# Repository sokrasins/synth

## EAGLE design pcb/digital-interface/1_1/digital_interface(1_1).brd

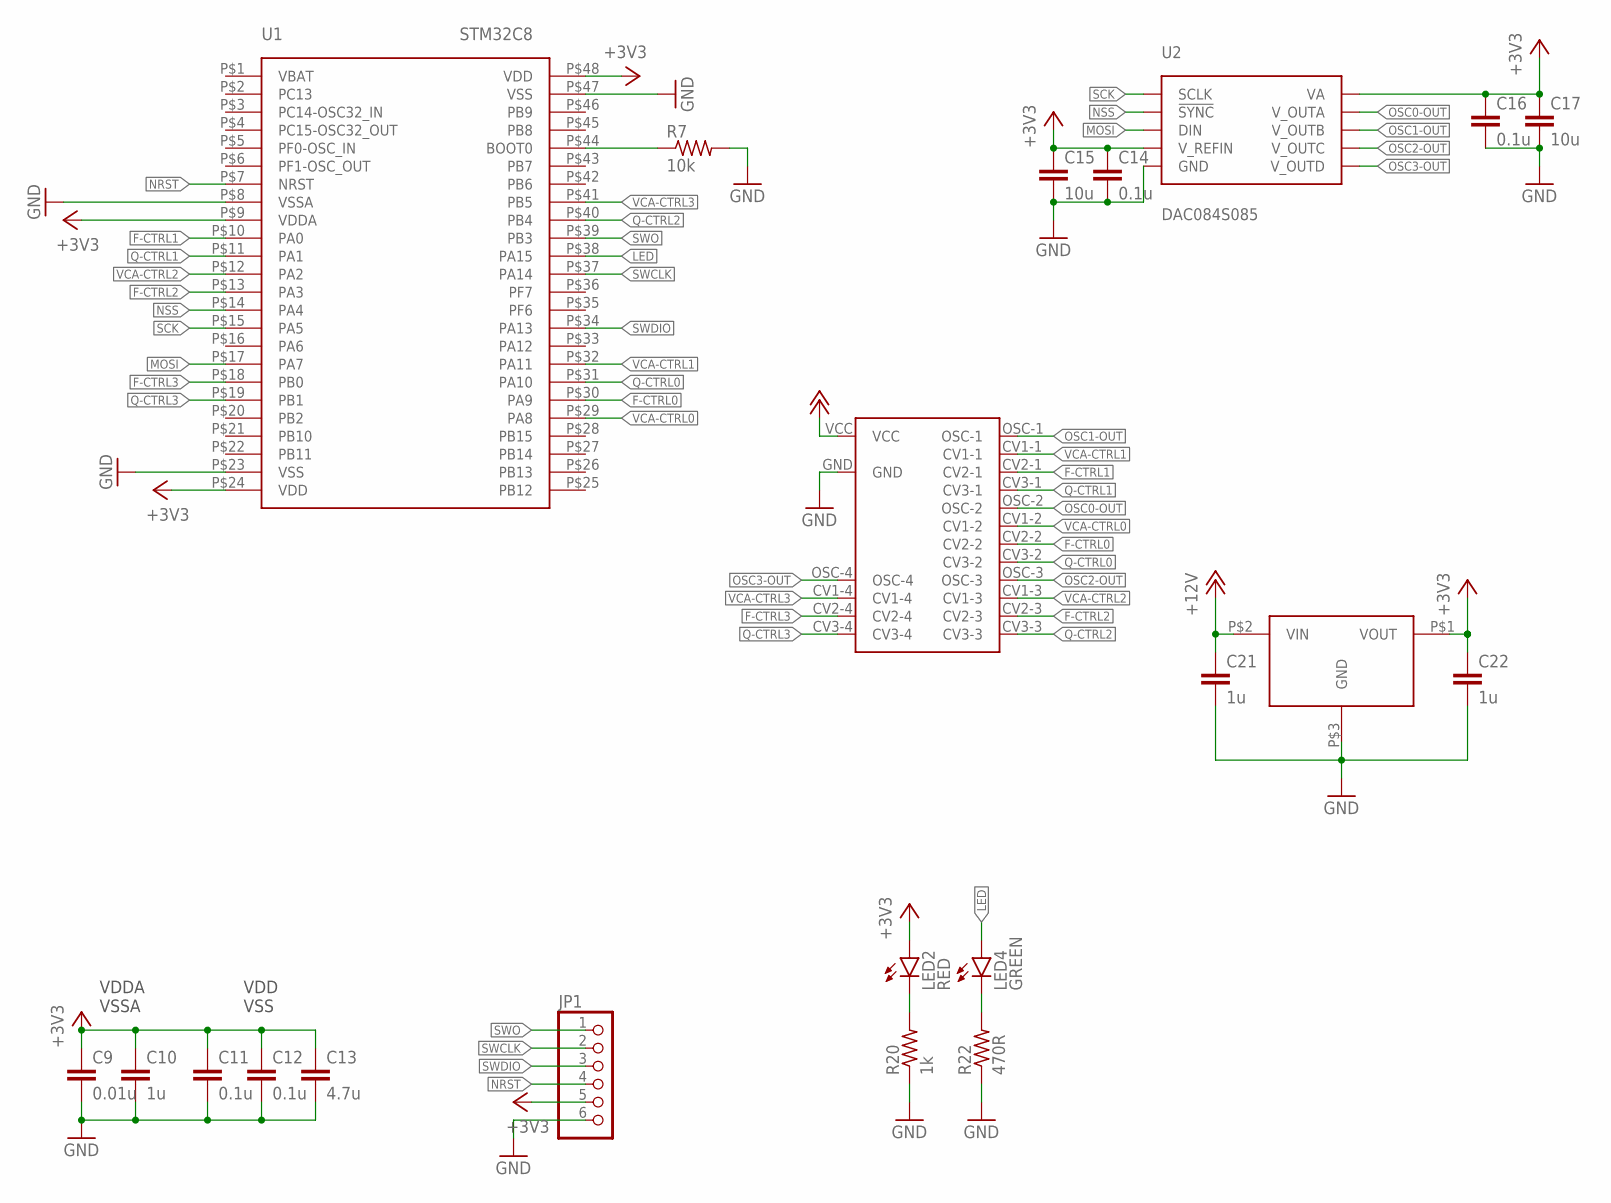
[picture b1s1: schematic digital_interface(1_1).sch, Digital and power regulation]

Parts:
C9: 0.01u; C0603
C10, C21, C22: 1u; C0603
C11, C12, C14, C16: 0.1u; C0603
C13: 4.7u; C0603
C15, C17: 10u; C0603
JP1: PINHD-1X6; 1X06
LED2: RED; 1206
LED4: GREEN; 1206
R7: 10k; R0603
R20: 1k; R0603
R22: 470R; R0603
U1: STM32C8; LQFP48
U2: DAC084S085; VSSOP10
U3: TLV760; SOT23-3
U$1: CV_MODULE

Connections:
+3V3: C9.1, C10.1, C11.1, C12.1, C13.1, C14.1, C15.1, C16.1, C17.1, C22.1, JP1.5, LED2.A, U1.P$9 (VDDA), U1.P$24 (VDD), U1.P$48 (VDD), U2.P$1 (VA), U2.P$7 (V_REFIN), U3.P$1 (VOUT)
+12V: C21.1, U3.P$2 (VIN), U$1.VCC
F-CTRL0: U1.P$30 (PA9), U$1.CV2-2
F-CTRL1: U1.P$10 (PA0), U$1.CV2-1
F-CTRL2: U1.P$13 (PA3), U$1.CV2-3
F-CTRL3: U1.P$18 (PB0), U$1.CV2-4
GND: C9.2, C10.2, C11.2, C12.2, C13.2, C14.2, C15.2, C16.2, C17.2, C21.2, C22.2, JP1.6, R7.2, R20.1, R22.1, U1.P$8 (VSSA), U1.P$23 (VSS), U1.P$47 (VSS), U2.P$6 (GND), U3.P$3 (GND), U$1.GND
LED: LED4.A, U1.P$38 (PA15)
MOSI: U1.P$17 (PA7), U2.P$8 (DIN)
unnamed: R7.1, U1.P$44 (BOOT0)
unnamed: LED2.C, R20.2
unnamed: LED4.C, R22.2
NRST: JP1.4, U1.P$7 (NRST)
NSS: U1.P$14 (PA4), U2.P$9 (!SYNC)
OSC0-OUT: U2.P$2 (V_OUTA), U$1.OSC-2
OSC1-OUT: U2.P$3 (V_OUTB), U$1.OSC-1
OSC2-OUT: U2.P$4 (V_OUTC), U$1.OSC-3
OSC3-OUT: U2.P$5 (V_OUTD), U$1.OSC-4
Q-CTRL0: U1.P$31 (PA10), U$1.CV3-2
Q-CTRL1: U1.P$11 (PA1), U$1.CV3-1
Q-CTRL2: U1.P$40 (PB4), U$1.CV3-3
Q-CTRL3: U1.P$19 (PB1), U$1.CV3-4
SCK: U1.P$15 (PA5), U2.P$10 (SCLK)
SWCLK: JP1.2, U1.P$37 (PA14)
SWDIO: JP1.3, U1.P$34 (PA13)
SWO: JP1.1, U1.P$39 (PB3)
VCA-CTRL0: U1.P$29 (PA8), U$1.CV1-2
VCA-CTRL1: U1.P$32 (PA11), U$1.CV1-1
VCA-CTRL2: U1.P$12 (PA2), U$1.CV1-3
VCA-CTRL3: U1.P$41 (PB5), U$1.CV1-4

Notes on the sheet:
VDDA VSSA
VDD VSS

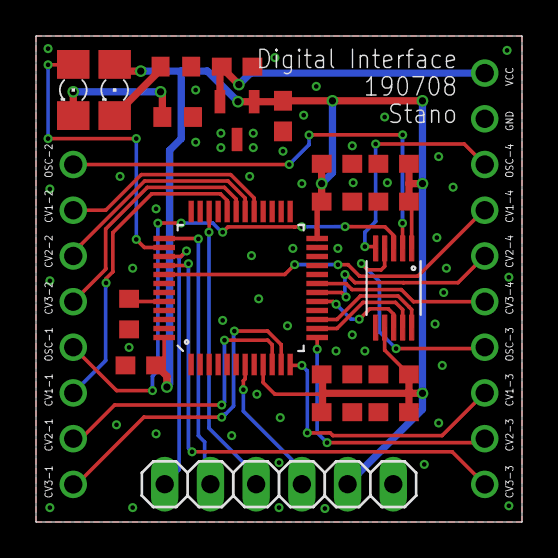
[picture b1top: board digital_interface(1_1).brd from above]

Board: 2 copper layers, 27.0 x 27.0 mm, 21 parts (0 on the bottom side), 30 nets.

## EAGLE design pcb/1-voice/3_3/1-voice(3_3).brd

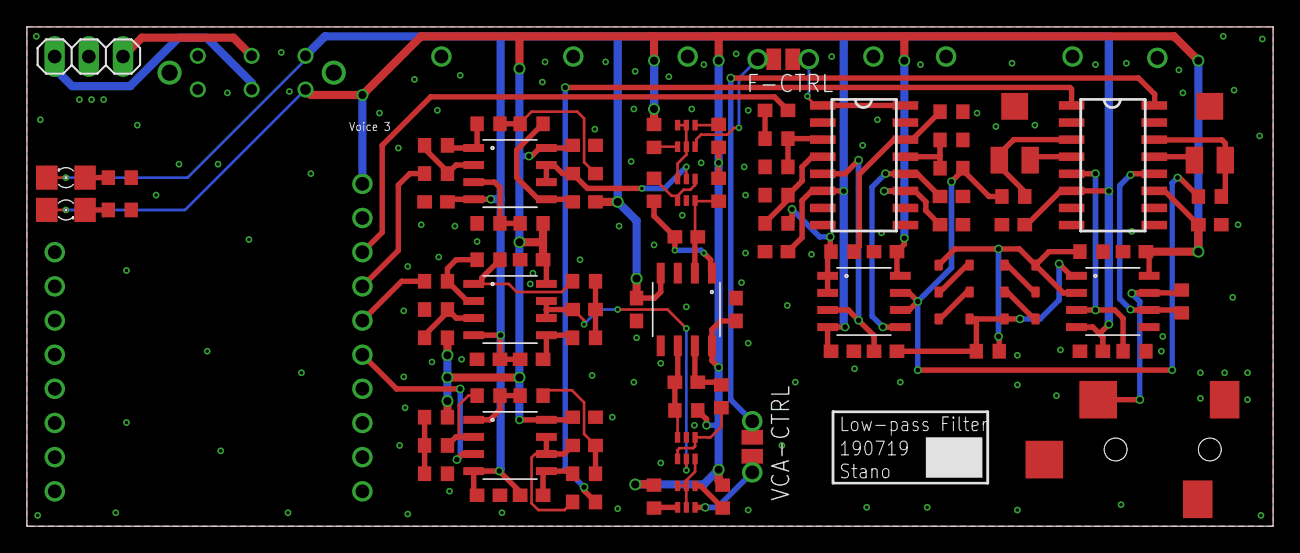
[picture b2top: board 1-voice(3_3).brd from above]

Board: 2 copper layers, 92.6 x 37.1 mm, 98 parts (0 on the bottom side), 68 nets.

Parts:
C1, C20: 10p; C0603
C2: 10u; C0603
C3, C23, C28: 1000p; C0603
C4, C24, C27, C35, C36: 2000p; C0603
C5, C6, C7, C8, C18, C19, C25, C26, C29, C30, C31, C32, C33, C34, C37, C38: 0.1u; C0603
D1, D2, D3, D4, D5, D6: 1N4148; SOD-323
JP2: 1X03
JP7: TRS
LED1: BLUE; 1206
LED3: YELLOW; 1206
Q1, Q3: BC847BS; SOT-363-JBLMASK
Q2, Q4: BC857BS; SOT-363-JBLMASK
R1, R36, R38: 3.3k; R0603
R2, R25, R45: 30k; R0603
R3, R4, R5, R10, R11, R12, R21, R26, R29, R33, R35, R37, R43, R44: 10k; R0603
R6, R13: 165k; R0603
R8, R14: 1k; R0603
R9: 280k; R0603
R15, R17: 562; R0603
R16, R18: 72k; R0603
R19, R39: 100k; R0603
R23, R24, R31, R46: 10; R0603
R27, R30, R32, R34: 220; R0603
R28: 562k; R0603
R40: 14.7k; R0603
R41: 1.62k; R0603
R42: 8.45k; R0603
SW1: SWITCH-DPDT; DPDT
U4, U5, U7, U9, U10, U11: TL072; SOIC8
U6, U8: LM13700; DMP16
U$1: CV_MODULE
U$2, U$3: CURRENT_TESTPOINT
VR1, VR2: 1k; POT-TRIM-SMD-BOURNS-3314

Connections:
12V-IN: JP2.3, SW1.P$5
+12V: C5.2, C8.2, C18.2, C25.2, C29.1, C31.2, C33.1, C37.1, LED1.A, R9.2, R16.1, R18.1, R23.2, R24.2, R28.2, R31.2, R42.2, R46.2, SW1.P$4, U4.P$8, U5.P$8, U6.11, U7.P$8, U8.11, U9.P$8, U10.P$8, U11.P$8, U$1.VCC
-12V: C3.2, C6.1, C7.1, C19.1, C23.2, C26.1, C28.2, C30.2, C32.1, C34.2, C38.2, LED3.C, SW1.P$1, U4.P$4, U5.P$4, U6.6, U7.P$4, U8.6, U9.P$4, U10.P$4, U11.P$4
-12V-IN: JP2.1, SW1.P$2
F0-OUT: R2.1, R25.2, R35.2, U7.P$6, U7.P$7
F-CTRL0: R13.2, U$1.CV1-4
F-CTRL0-EXP: U6.1, U6.16, U$2.P1, U$2.P1.1
F-CTRL0-LIN: C24.2, Q1.2, U4.P$6, U4.P$7
FILT_IN: C2.2, R26.1
GND: C5.1, C6.2, C7.2, C8.1, C18.1, C19.2, C25.1, C26.2, C29.2, C30.1, C31.1, C32.2, C33.2, C34.1, C36.2, C37.2, C38.1, JP2.2, JP7.P$1, Q1.5, Q3.2, R15.2, R17.2, R19.1, R21.1, R27.1, R30.2, R32.2, R34.2, R36.1, R38.1, R41.1, U9.P$3, U9.P$5, U11.P$5, U$1.GND, VR1.2, VR2.2
unnamed: R10.2, R13.1, U4.P$2
unnamed: R1.2, U8.12, U11.P$6
unnamed: R2.2, U8.14, VR2.1
unnamed: C3.1, R3.2, U10.P$5
unnamed: C4.1, R3.1, R4.2
unnamed: R4.1, R5.1, U10.P$1
unnamed: Q2.6, U$2.P2, U$2.P2.1
unnamed: Q4.6, U$3.P2, U$3.P2.1
unnamed: Q1.1, Q1.4, R8.2
unnamed: C20.2, R8.1, U9.P$1
unnamed: C20.1, Q1.6, R9.1, U9.P$2
unnamed: C23.1, R11.2, U4.P$5
unnamed: Q1.3, Q2.2, Q2.3, Q2.5
unnamed: C24.1, R11.1, R12.2
unnamed: R10.1, R12.1, U4.P$1
unnamed: Q3.1, Q3.4, R14.2
unnamed: LED1.C, R19.2
unnamed: R5.2, R6.1, U10.P$2
unnamed: R15.1, R16.2, U4.P$3
unnamed: LED3.A, R21.2
unnamed: Q2.4, R23.1
unnamed: Q2.1, R24.1
unnamed: C36.1, U6.12, U7.P$5
unnamed: R26.2, R27.2, U6.3
unnamed: C35.1, U6.5, U7.P$3
unnamed: R36.2, U8.5, U11.P$3
unnamed: U8.4, VR1.1
unnamed: R29.1, R30.1, U6.4
unnamed: D1.2, D6.1, R37.1, R38.2, U11.P$2
unnamed: C1.2, R14.1, U9.P$7
unnamed: C35.2, D3.1, D4.2, R37.2, U11.P$1
unnamed: R32.1, R33.2, U6.14
unnamed: R34.1, R35.1, U6.13
unnamed: D2.1, D3.2
unnamed: D1.1, D2.2
unnamed: D4.1, D5.2
unnamed: D5.1, D6.2
unnamed: R40.1, R41.2, R42.1
unnamed: R39.1, R40.2, U5.P$2
unnamed: R39.2, R43.1, U5.P$1
unnamed: C27.1, R43.2, R44.1
unnamed: C28.1, R44.2, U5.P$5
unnamed: R45.1, U8.1
unnamed: U8.13, VR2.3
unnamed: C1.1, Q3.3, R28.1, U9.P$6
unnamed: R29.2, R33.1, U7.P$1, U7.P$2
unnamed: R17.1, R18.2, U10.P$3
unnamed: Q3.6, Q4.2, Q4.3, Q4.5
unnamed: Q4.4, R31.1
unnamed: Q4.1, R46.1
unnamed: R25.1, U8.3, VR1.3
OSC0-OUT: C2.1, U$1.OSC-4
Q-CTRL0: U5.P$3, U$1.CV3-4
Q-CTRL0-I: C27.2, R45.2, U5.P$6, U5.P$7
VCA0-EXP: U8.16, U$3.P1, U$3.P1.1
VCA0-LP: C4.2, Q3.5, U10.P$6, U10.P$7
VCA-CTRL0: R6.2, U$1.CV2-4
VCA-OUT0: JP7.P$2, R1.1, U11.P$7

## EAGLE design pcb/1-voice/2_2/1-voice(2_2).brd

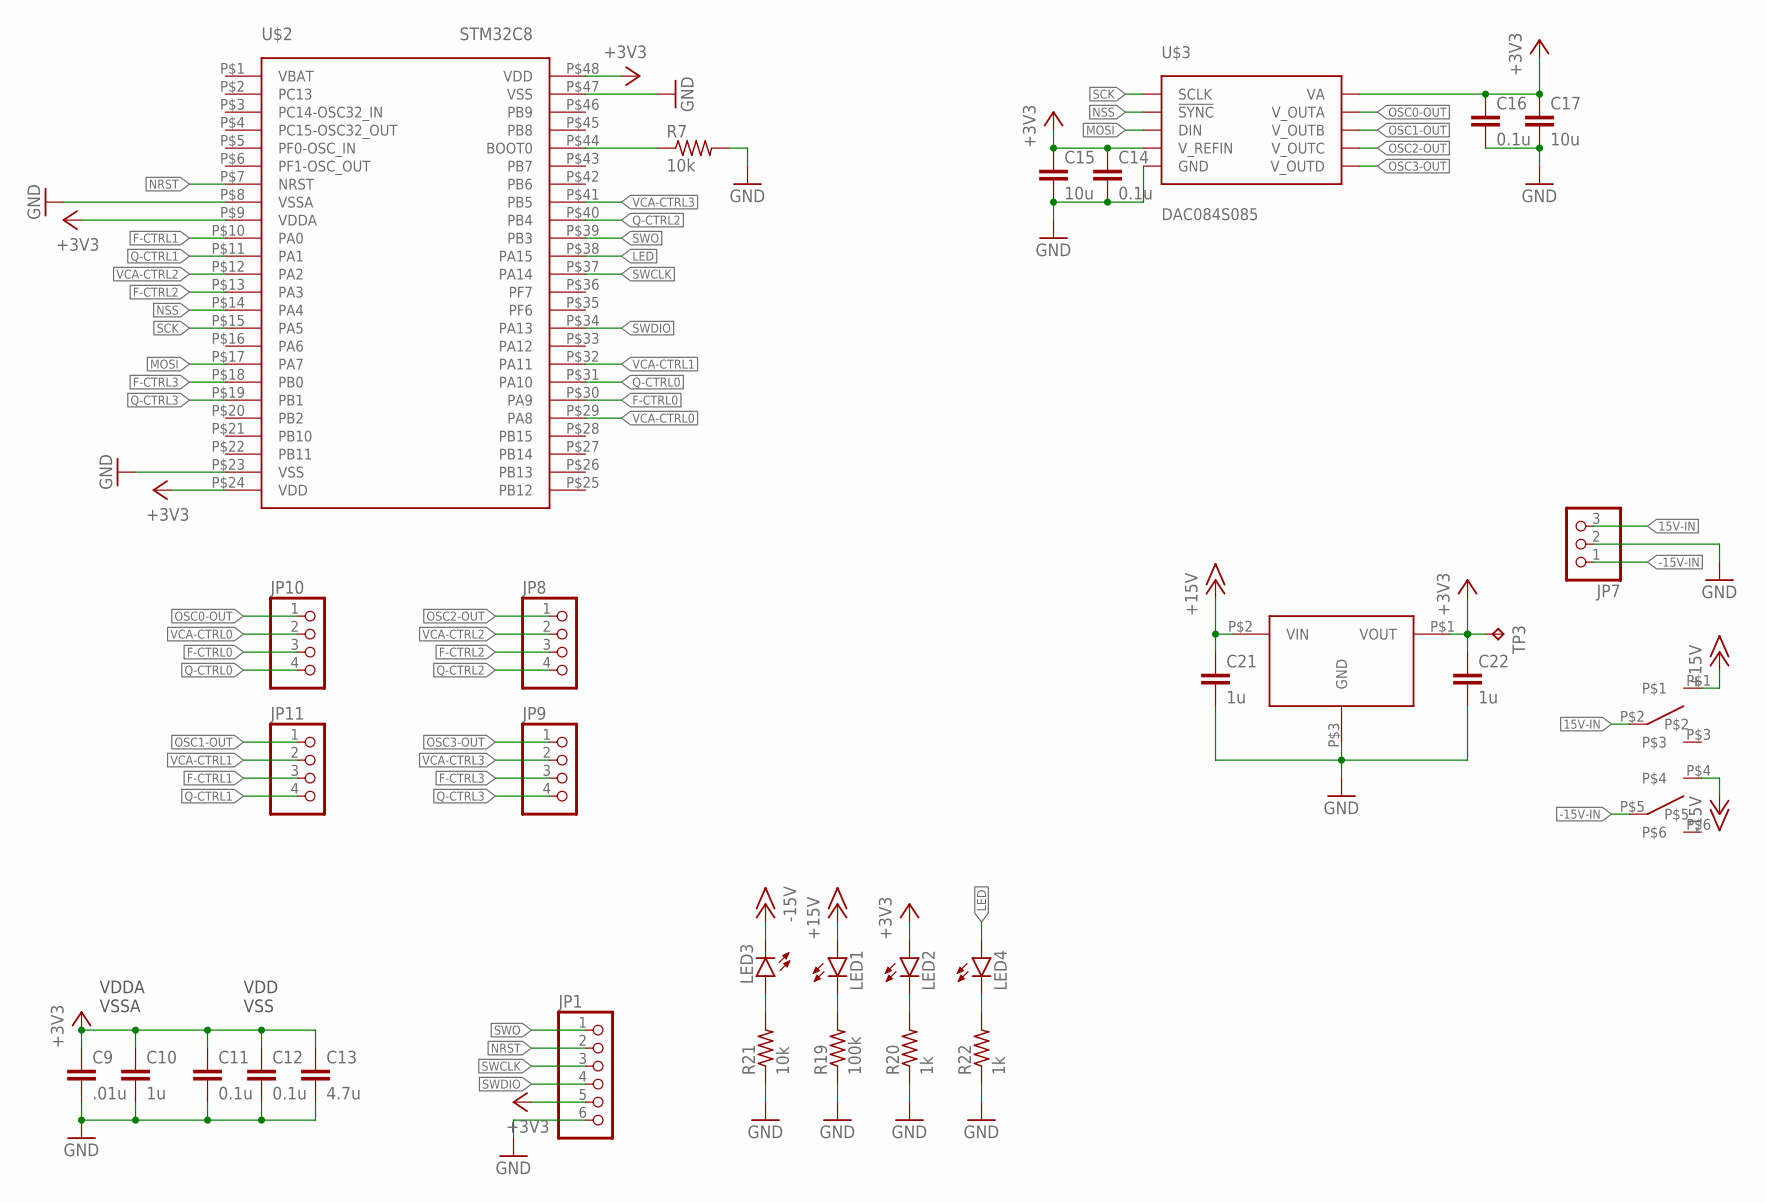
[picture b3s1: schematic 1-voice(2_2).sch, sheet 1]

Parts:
C9: .01u; C0603
C10, C21, C22: 1u; C0603
C11, C12, C14, C16: 0.1u; C0603
C13: 4.7u; C0603
C15, C17: 10u; C0603
JP1: PINHD-1X6; 1X06
JP7: PINHD-1X3; 1X03
JP8, JP9, JP10, JP11: PINHD-1X4; 1X04
LED1, LED2, LED3, LED4: LEDSMT1206; 1206
R7, R21: 10k; R0603
R19: 100k; R0603
R20, R22: 1k; R0603
TP3: TPPAD1-13; P1-13
U$2: STM32C8; LQFP48
U$3: DAC084S085; VSSOP10
U$4: TLV760; SOT23-3
U$6: SWITCH-DPDT; DPDT

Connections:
15V-IN: JP7.3, U$6.P$2
+3V3: C9.1, C10.1, C11.1, C12.1, C13.1, C14.1, C15.1, C16.1, C17.1, C22.1, JP1.5, LED2.A, TP3.TP, U$2.P$9 (VDDA), U$2.P$24 (VDD), U$2.P$48 (VDD), U$3.P$1 (VA), U$3.P$7 (V_REFIN), U$4.P$1 (VOUT); also elsewhere on the board
+15V: C21.1, LED1.A, U$4.P$2 (VIN), U$6.P$1; also elsewhere on the board
-15V: LED3.C, U$6.P$4; also elsewhere on the board
-15V-IN: JP7.1, U$6.P$5
F-CTRL0: JP10.3, U$2.P$30 (PA9); also elsewhere on the board
F-CTRL1: JP11.3, U$2.P$10 (PA0)
F-CTRL2: JP8.3, U$2.P$13 (PA3)
F-CTRL3: JP9.3, U$2.P$18 (PB0)
GND: C9.2, C10.2, C11.2, C12.2, C13.2, C14.2, C15.2, C16.2, C17.2, C21.2, C22.2, JP1.6, JP7.2, R7.2, R19.1, R20.1, R21.1, R22.1, U$2.P$8 (VSSA), U$2.P$23 (VSS), U$2.P$47 (VSS), U$3.P$6 (GND), U$4.P$3 (GND); also elsewhere on the board
LED: LED4.A, U$2.P$38 (PA15)
MOSI: U$2.P$17 (PA7), U$3.P$8 (DIN)
unnamed: R7.1, U$2.P$44 (BOOT0)
unnamed: LED1.C, R19.2
unnamed: LED2.C, R20.2
unnamed: LED3.A, R21.2
unnamed: LED4.C, R22.2
NRST: JP1.2, U$2.P$7 (NRST)
NSS: U$2.P$14 (PA4), U$3.P$9 (!SYNC)
OSC0-OUT: JP10.1, U$3.P$2 (V_OUTA); also elsewhere on the board
OSC1-OUT: JP11.1, U$3.P$3 (V_OUTB)
OSC2-OUT: JP8.1, U$3.P$4 (V_OUTC)
OSC3-OUT: JP9.1, U$3.P$5 (V_OUTD)
Q-CTRL0: JP10.4, U$2.P$31 (PA10)
Q-CTRL1: JP11.4, U$2.P$11 (PA1)
Q-CTRL2: JP8.4, U$2.P$40 (PB4)
Q-CTRL3: JP9.4, U$2.P$19 (PB1)
SCK: U$2.P$15 (PA5), U$3.P$10 (SCLK)
SWCLK: JP1.3, U$2.P$37 (PA14)
SWDIO: JP1.4, U$2.P$34 (PA13)
SWO: JP1.1, U$2.P$39 (PB3)
VCA-CTRL0: JP10.2, U$2.P$29 (PA8); also elsewhere on the board
VCA-CTRL1: JP11.2, U$2.P$32 (PA11)
VCA-CTRL2: JP8.2, U$2.P$12 (PA2)
VCA-CTRL3: JP9.2, U$2.P$41 (PB5)

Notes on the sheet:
VDDA VSSA
VDD VSS

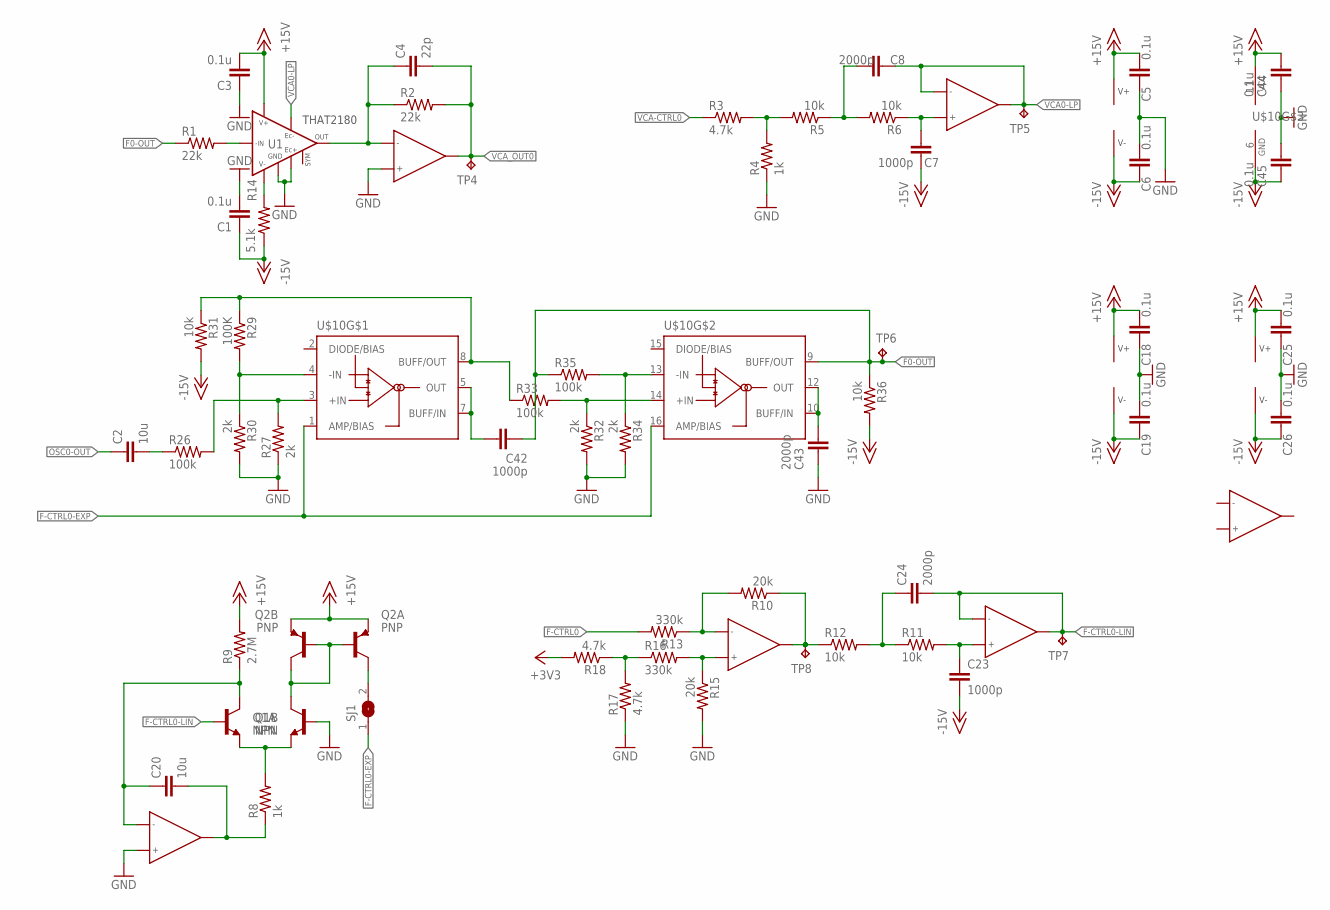
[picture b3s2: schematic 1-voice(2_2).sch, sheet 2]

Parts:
C1, C3, C5, C6, C18, C19, C25, C26, C44, C45: 0.1u; C0603
C2, C20: 10u; C0603
C4: 22p; C0603
C7, C23, C42: 1000p; C0603
C8, C24, C43: 2000p; C0603
Q1: NPN; SOT-363-JBLMASK
Q2: PNP; SOT-363-JBLMASK
R1, R2: 22k; R0603
R3, R17, R18: 4.7k; R0603
R4, R8: 1k; R0603
R5, R6, R11, R12, R31, R36: 10k; R0603
R9: 2.7M; R0603
R10, R15: 20k; R0603
R13, R16: 330k; R0603
R14: 5.1k; R0603
R26, R33, R35: 100k; R0603
R27, R30, R32, R34: 2k; R0603
R29: 100K; R0603
SJ1: SJ
TP4, TP5, TP6, TP7, TP8: TPPAD1-13; P1-13
U1: THAT2180; SIP8
U$1, U$5, U$11: TL072; SOIC8
U$10: XX-13700DMP16; DMP16

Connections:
+3V3: R18.2; also elsewhere on the board
+15V: C3.2, C5.2, C18.2, C25.2, C44.1, Q2.1 (E), Q2.4 (E), R9.2, U1.$P7 (V+), U$1.P$8 (V+), U$5.P$8 (V+), U$10.11 (VCC), U$11.P$8 (V+); also elsewhere on the board
-15V: C1.1, C6.1, C7.1, C19.1, C23.2, C26.1, C45.2, R14.1, R31.2, R36.2, U$1.P$4 (V-), U$5.P$4 (V-), U$10.6 (GND), U$11.P$4 (V-); also elsewhere on the board
F0-OUT: C42.2, R1.1, R35.1, R36.1, TP6.TP, U$10.9 (BUFF/OUT)
F-CTRL0: R13.2; also elsewhere on the board
F-CTRL0-EXP: SJ1.1, U$10.1 (AMP/BIAS), U$10.16 (AMP/BIAS)
F-CTRL0-LIN: C24.2, Q1.2 (B), TP7.TP, U$11.P$6 (IN-), U$11.P$7 (OUT)
FILT_IN: C2.2, R26.1
GND: C1.2, C3.1, C5.1, C6.2, C18.1, C19.2, C25.1, C26.2, C43.2, C44.2, C45.1, Q1.5 (B), R4.1, R15.2, R17.1, R27.1, R30.2, R32.2, R34.2, U1.$P2 (EC+), U1.$P6 (GND), U$1.P$3 (IN+), U$11.P$3 (IN+); also elsewhere on the board
unnamed: R10.2, R13.1, U$5.P$6 (IN-)
unnamed: R1.2, U1.$P1 (-IN)
unnamed: C4.1, R2.1, U1.$P8 (OUT), U$1.P$2 (IN-)
unnamed: R3.2, R4.2, R5.2
unnamed: C8.2, R5.1, R6.2
unnamed: C7.2, R6.1, U$1.P$5 (IN+)
unnamed: Q2.6 (C), SJ1.2
unnamed: Q1.1 (E), Q1.4 (E), R8.2
unnamed: C20.2, R8.1, U$11.P$1 (OUT)
unnamed: C20.1, Q1.6 (C), R9.1, U$11.P$2 (IN-)
unnamed: C23.1, R11.2, U$11.P$5 (IN+)
unnamed: Q1.3 (C), Q2.2 (B), Q2.3 (C), Q2.5 (B)
unnamed: C24.1, R11.1, R12.2
unnamed: R10.1, R12.1, TP8.TP, U$5.P$7 (OUT)
unnamed: R14.2, U1.$P5 (V-)
unnamed: R16.1, R17.2, R18.1
unnamed: R15.1, R16.2, U$5.P$5 (IN+)
unnamed: R26.2, R27.2, U$10.3 (+IN)
unnamed: R29.2, R30.1, U$10.4 (-IN)
unnamed: C42.1, U$10.5 (OUT), U$10.7 (BUFF/IN)
unnamed: R29.1, R31.1, R33.1, U$10.8 (BUFF/OUT)
unnamed: C43.1, U$10.10 (BUFF/IN), U$10.12 (OUT)
unnamed: R32.1, R33.2, U$10.14 (+IN)
unnamed: R34.1, R35.2, U$10.13 (-IN)
OSC0-OUT: C2.1; also elsewhere on the board
VCA0-LP: C8.1, TP5.TP, U1.$P3 (EC-), U$1.P$6 (IN-), U$1.P$7 (OUT)
VCA-CTRL0: R3.1; also elsewhere on the board
VCA_OUT0: C4.2, R2.2, TP4.TP, U$1.P$1 (OUT)

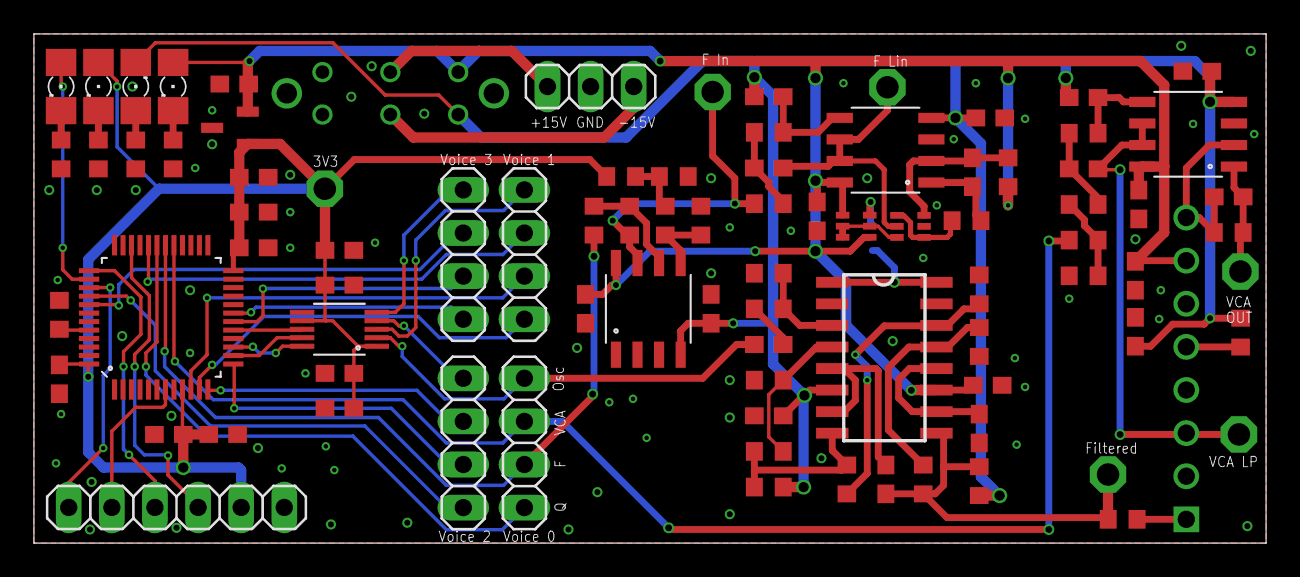
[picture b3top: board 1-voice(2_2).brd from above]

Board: 2 copper layers, 72.6 x 30.0 mm, 90 parts (1 on the bottom side), 65 nets.

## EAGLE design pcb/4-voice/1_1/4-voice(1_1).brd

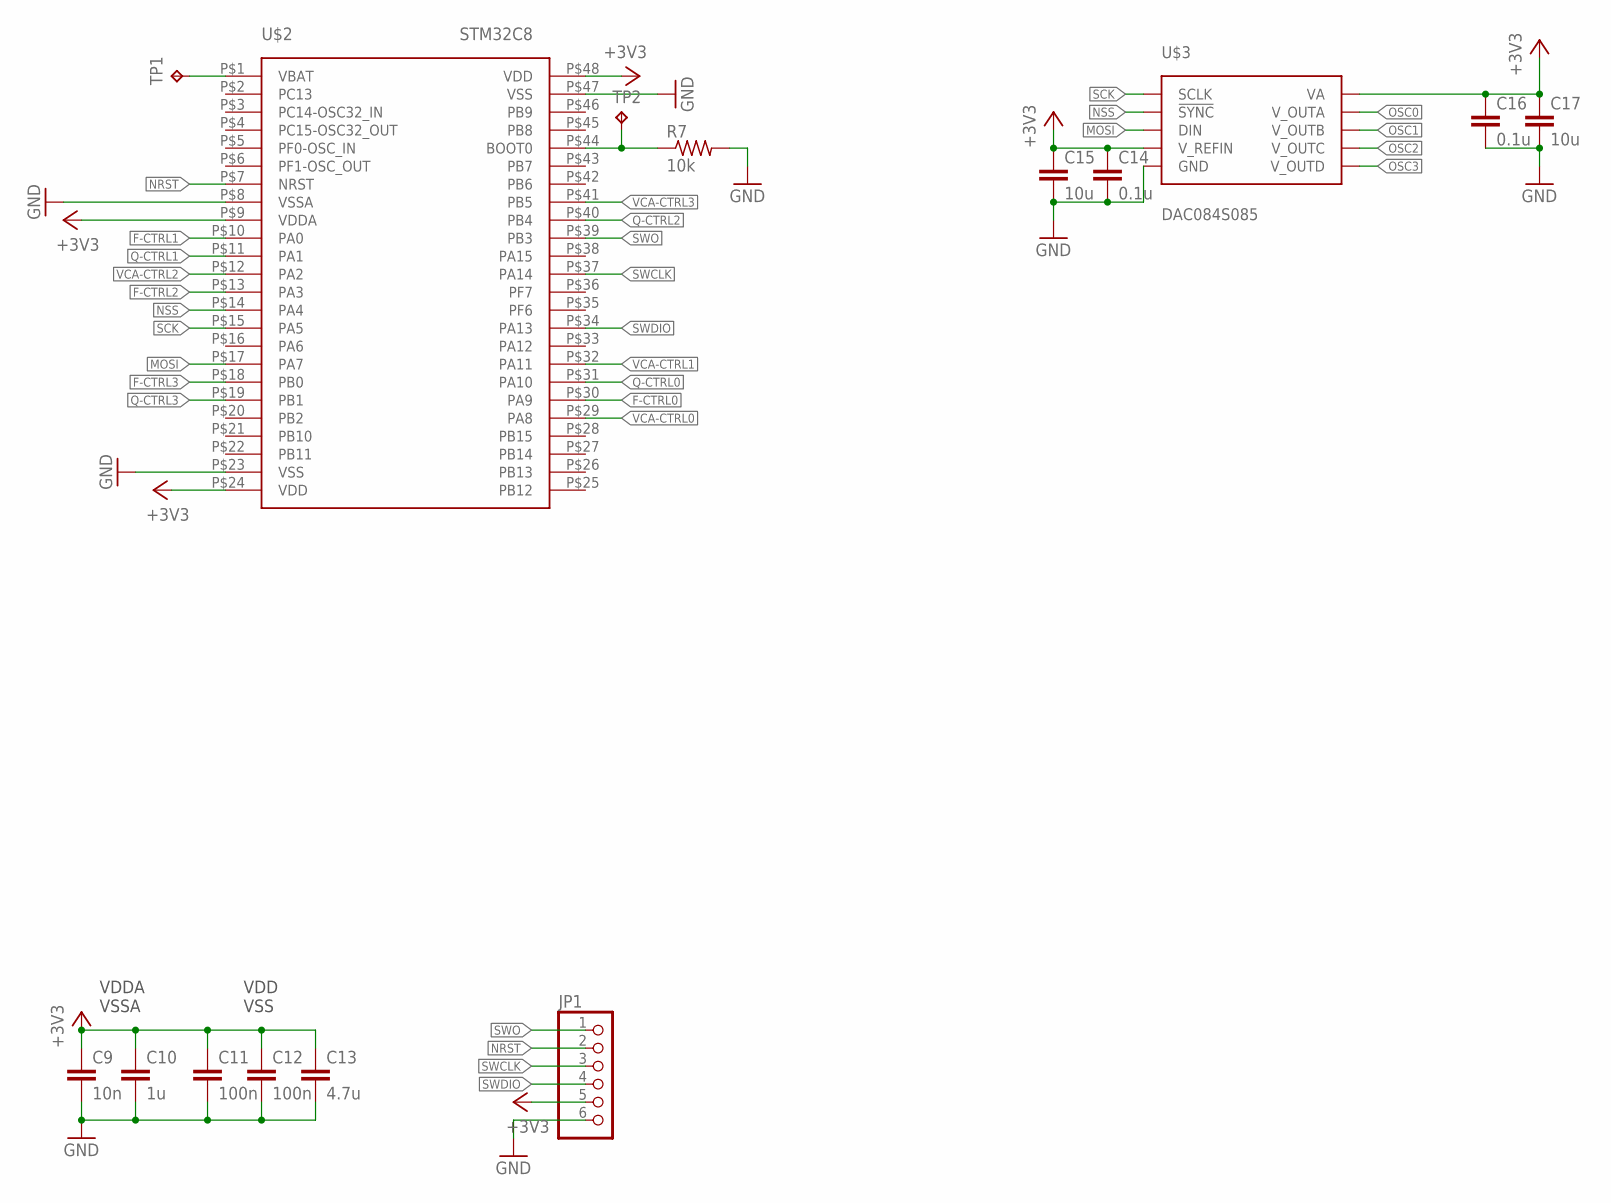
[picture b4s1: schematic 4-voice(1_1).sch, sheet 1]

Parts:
C9: 10n; C1206
C10: 1u; C1206
C11, C12: 100n; C1206
C13: 4.7u; C1206
C14, C16: 0.1u; C1206
C15, C17: 10u; C1206
JP1: PINHD-1X6; 1X06
R7: 10k; R1206
TP1, TP2: TPPAD1-13; P1-13
U$2: STM32C8; LQFP48
U$3: DAC084S085; VSSOP10

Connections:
+3V3: C9.1, C10.1, C11.1, C12.1, C13.1, C14.1, C15.1, C16.1, C17.1, JP1.5, U$2.P$9 (VDDA), U$2.P$24 (VDD), U$2.P$48 (VDD), U$3.P$1 (VA), U$3.P$7 (V_REFIN)
F-CTRL0: U$2.P$30 (PA9)
F-CTRL1: U$2.P$10 (PA0)
F-CTRL2: U$2.P$13 (PA3)
F-CTRL3: U$2.P$18 (PB0)
GND: C9.2, C10.2, C11.2, C12.2, C13.2, C14.2, C15.2, C16.2, C17.2, JP1.6, R7.2, U$2.P$8 (VSSA), U$2.P$23 (VSS), U$2.P$47 (VSS), U$3.P$6 (GND); also elsewhere on the board
MOSI: U$2.P$17 (PA7), U$3.P$8 (DIN)
unnamed: TP1.TP, U$2.P$1 (VBAT)
unnamed: R7.1, TP2.TP, U$2.P$44 (BOOT0)
NRST: JP1.2, U$2.P$7 (NRST)
NSS: U$2.P$14 (PA4), U$3.P$9 (!SYNC)
OSC0: U$3.P$2 (V_OUTA); also elsewhere on the board
OSC1: U$3.P$3 (V_OUTB); also elsewhere on the board
OSC2: U$3.P$4 (V_OUTC); also elsewhere on the board
OSC3: U$3.P$5 (V_OUTD); also elsewhere on the board
Q-CTRL0: U$2.P$31 (PA10)
Q-CTRL1: U$2.P$11 (PA1)
Q-CTRL2: U$2.P$40 (PB4)
Q-CTRL3: U$2.P$19 (PB1)
SCK: U$2.P$15 (PA5), U$3.P$10 (SCLK)
SWCLK: JP1.3, U$2.P$37 (PA14)
SWDIO: JP1.4, U$2.P$34 (PA13)
SWO: JP1.1, U$2.P$39 (PB3)
VCA-CTRL0: U$2.P$29 (PA8); also elsewhere on the board
VCA-CTRL1: U$2.P$32 (PA11); also elsewhere on the board
VCA-CTRL2: U$2.P$12 (PA2); also elsewhere on the board
VCA-CTRL3: U$2.P$41 (PB5); also elsewhere on the board

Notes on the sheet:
VDDA VSSA
VDD VSS

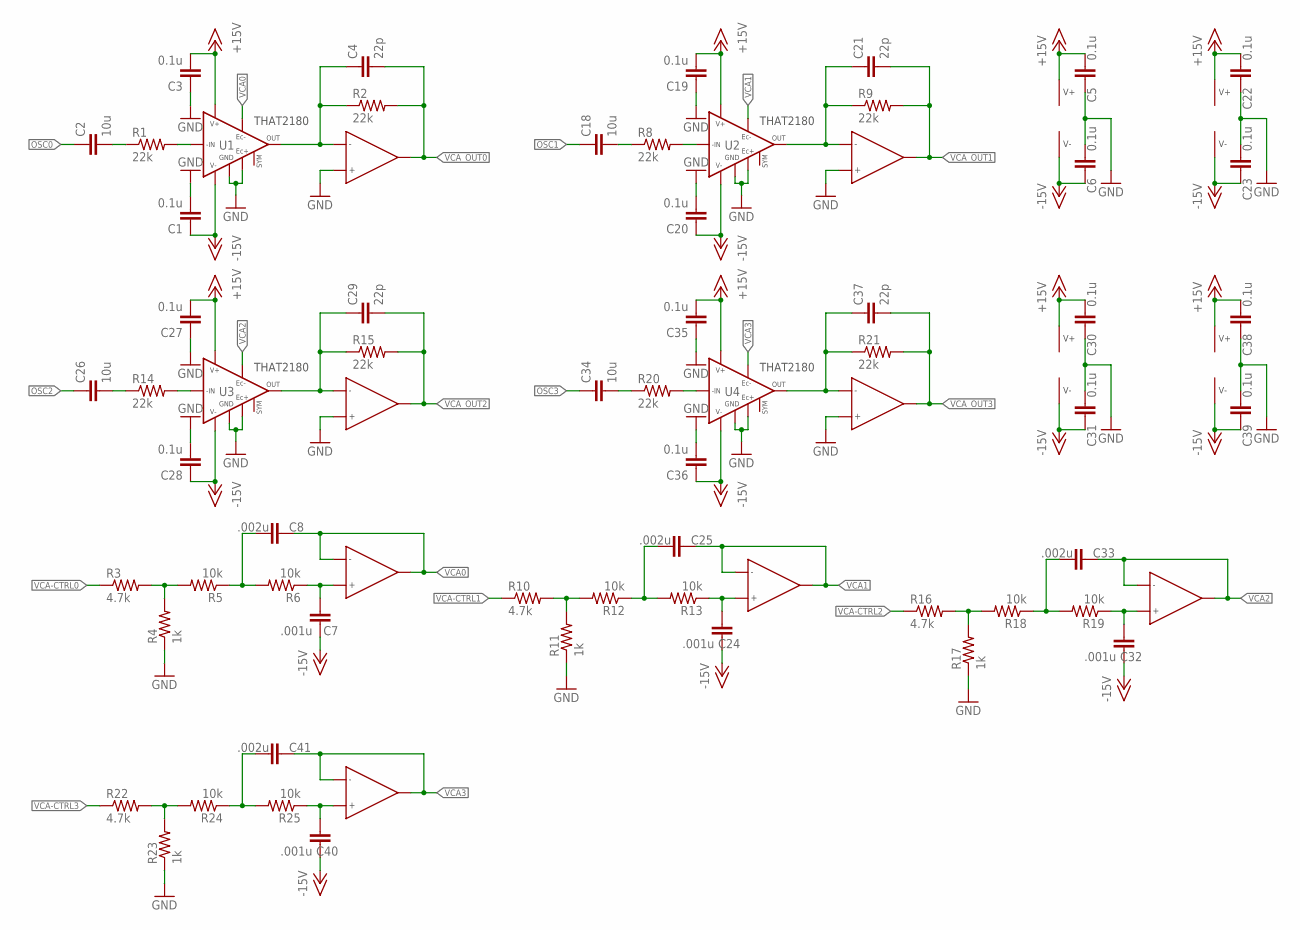
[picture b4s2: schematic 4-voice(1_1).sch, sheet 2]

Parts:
C1, C3, C5, C6, C19, C20, C22, C23, C27, C28, C30, C31, C35, C36, C38, C39: 0.1u; C1206
C2, C18, C26, C34: 10u; C1206
C4, C21, C29, C37: 22p; C1206
C7, C24, C32, C40: .001u; C1206
C8, C25, C33, C41: .002u; C1206
R1, R2, R8, R9, R14, R15, R20, R21: 22k; R1206
R3, R10, R16, R22: 4.7k; R1206
R4, R11, R17, R23: 1k; R1206
R5, R6, R12, R13, R18, R19, R24, R25: 10k; R1206
U1, U2, U3, U4: THAT2180; SIP8
U$1, U$4, U$5, U$6, U$7, U$8, U$9: TL072; SOIC8

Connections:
+15V: C3.2, C5.2, C19.2, C22.2, C27.2, C30.2, C35.2, C38.2, U1.$P7 (V+), U2.$P7 (V+), U3.$P7 (V+), U4.$P7 (V+), U$1.P$8 (V+), U$4.P$8 (V+), U$6.P$8 (V+), U$8.P$8 (V+); also elsewhere on the board
-15V: C1.1, C6.1, C7.1, C20.1, C23.1, C24.1, C28.1, C31.1, C32.1, C36.1, C39.1, C40.1, U1.$P5 (V-), U2.$P5 (V-), U3.$P5 (V-), U4.$P5 (V-), U$1.P$4 (V-), U$4.P$4 (V-), U$6.P$4 (V-), U$8.P$4 (V-); also elsewhere on the board
GND: C1.2, C3.1, C5.1, C6.2, C19.1, C20.2, C22.1, C23.2, C27.1, C28.2, C30.1, C31.2, C35.1, C36.2, C38.1, C39.2, R4.1, R11.1, R17.1, R23.1, U1.$P2 (EC+), U1.$P6 (GND), U2.$P2 (EC+), U2.$P6 (GND), U3.$P2 (EC+), U3.$P6 (GND), U4.$P2 (EC+), U4.$P6 (GND), U$1.P$3 (IN+), U$4.P$3 (IN+), U$5.P$3 (IN+), U$7.P$3 (IN+); also elsewhere on the board
unnamed: C2.2, R1.1
unnamed: R1.2, U1.$P1 (-IN)
unnamed: C4.1, R2.1, U1.$P8 (OUT), U$1.P$2 (IN-)
unnamed: R3.2, R4.2, R5.2
unnamed: C8.2, R5.1, R6.2
unnamed: C7.2, R6.1, U$1.P$5 (IN+)
unnamed: C18.2, R8.1
unnamed: R8.2, U2.$P1 (-IN)
unnamed: C21.1, R9.1, U2.$P8 (OUT), U$4.P$2 (IN-)
unnamed: R10.2, R11.2, R12.2
unnamed: C25.2, R12.1, R13.2
unnamed: C24.2, R13.1, U$4.P$5 (IN+)
unnamed: C26.2, R14.1
unnamed: R14.2, U3.$P1 (-IN)
unnamed: C29.1, R15.1, U3.$P8 (OUT), U$5.P$2 (IN-)
unnamed: R16.2, R17.2, R18.2
unnamed: C33.2, R18.1, R19.2
unnamed: C32.2, R19.1, U$6.P$5 (IN+)
unnamed: C34.2, R20.1
unnamed: R20.2, U4.$P1 (-IN)
unnamed: C37.1, R21.1, U4.$P8 (OUT), U$7.P$2 (IN-)
unnamed: R22.2, R23.2, R24.2
unnamed: C41.2, R24.1, R25.2
unnamed: C40.2, R25.1, U$9.P$5 (IN+)
OSC0: C2.1; also elsewhere on the board
OSC1: C18.1; also elsewhere on the board
OSC2: C26.1; also elsewhere on the board
OSC3: C34.1; also elsewhere on the board
VCA0: C8.1, U1.$P3 (EC-), U$1.P$6 (IN-), U$1.P$7 (OUT)
VCA1: C25.1, U2.$P3 (EC-), U$4.P$6 (IN-), U$4.P$7 (OUT)
VCA2: C33.1, U3.$P3 (EC-), U$6.P$6 (IN-), U$6.P$7 (OUT)
VCA3: C41.1, U4.$P3 (EC-), U$9.P$6 (IN-), U$9.P$7 (OUT)
VCA-CTRL0: R3.1; also elsewhere on the board
VCA-CTRL1: R10.1; also elsewhere on the board
VCA-CTRL2: R16.1; also elsewhere on the board
VCA-CTRL3: R22.1; also elsewhere on the board
VCA_OUT0: C4.2, R2.2, U$1.P$1 (OUT)
VCA_OUT1: C21.2, R9.2, U$4.P$1 (OUT)
VCA_OUT2: C29.2, R15.2, U$5.P$1 (OUT)
VCA_OUT3: C37.2, R21.2, U$7.P$1 (OUT)

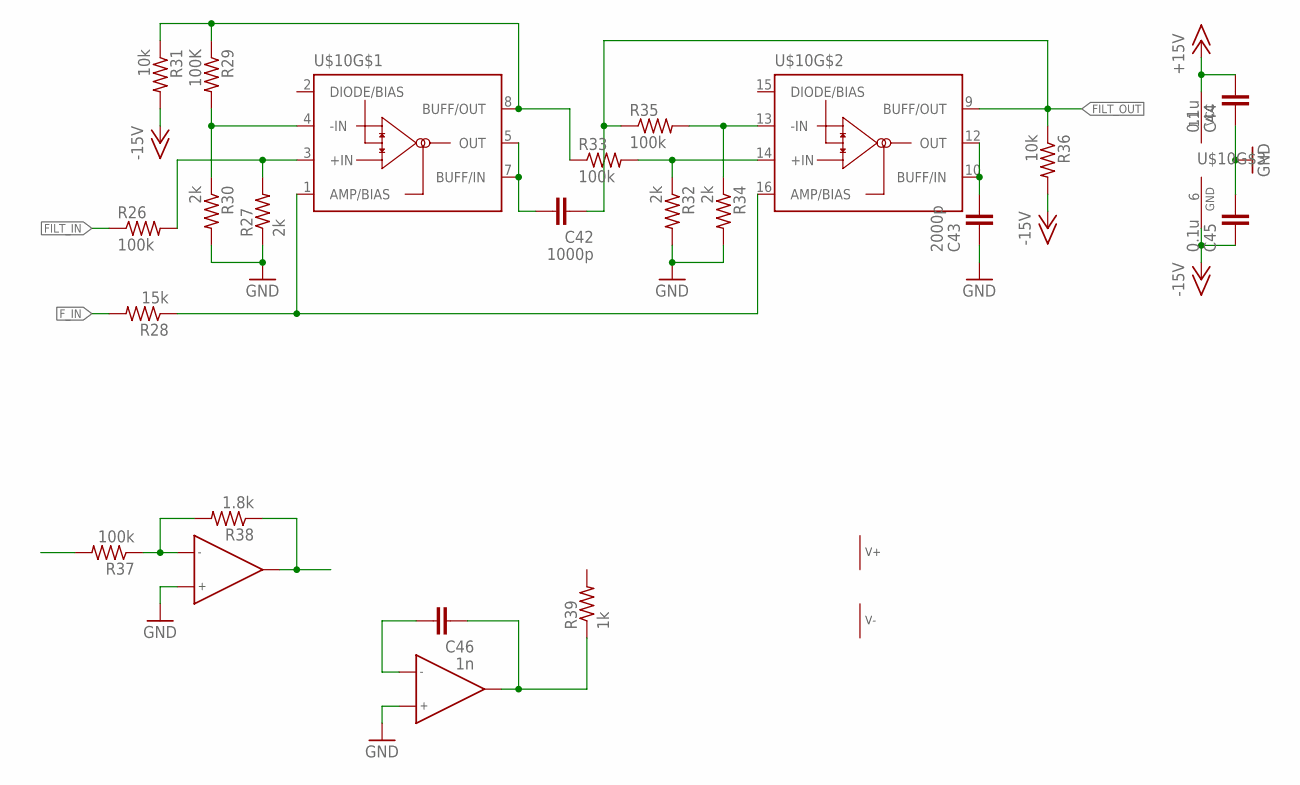
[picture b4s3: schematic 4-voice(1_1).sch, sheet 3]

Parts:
C42: 1000p; C1206
C43: 2000p; C1206
C44, C45: 0.1u; C1206
C46: 1n; C1206
R26, R33, R35, R37: 100k; R1206
R27, R30, R32, R34: 2k; R1206
R28: 15k; R1206
R29: 100K; R1206
R31, R36: 10k; R1206
R38: 1.8k; R1206
R39: 1k; R1206
U$10: XX-13700DMP16; DMP16
U$11: TL072; SOIC8

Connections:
+15V: C44.1, U$10.11 (VCC); also elsewhere on the board
-15V: C45.2, R31.2, R36.2, U$10.6 (GND); also elsewhere on the board
FILT_IN: R26.1
FILT_OUT: C42.2, R35.1, R36.1, U$10.9 (BUFF/OUT)
F_IN: R28.2
GND: C43.2, C44.2, C45.1, R27.1, R30.2, R32.2, R34.2, U$11.P$3 (IN+), U$11.P$5 (IN+); also elsewhere on the board
unnamed: R26.2, R27.2, U$10.3 (+IN)
unnamed: R28.1, U$10.1 (AMP/BIAS), U$10.16 (AMP/BIAS)
unnamed: R37.1, R38.2, U$11.P$2 (IN-)
unnamed: R29.2, R30.1, U$10.4 (-IN)
unnamed: C42.1, U$10.5 (OUT), U$10.7 (BUFF/IN)
unnamed: R29.1, R31.1, R33.1, U$10.8 (BUFF/OUT)
unnamed: C43.1, U$10.10 (BUFF/IN), U$10.12 (OUT)
unnamed: R32.1, R33.2, U$10.14 (+IN)
unnamed: R34.1, R35.2, U$10.13 (-IN)
unnamed: R38.1, U$11.P$1 (OUT)
unnamed: C46.2, R39.1, U$11.P$7 (OUT)
unnamed: C46.1, U$11.P$6 (IN-)

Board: 2 copper layers, 103 parts (0 on the bottom side), 66 nets, no tracks yet.

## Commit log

2019-04-13 set up sample clock timer
2019-04-13 Added datasheets
2019-04-14 square osc working with dac
2019-04-14 Futz around with api, and add VCA files
2019-04-14 add one more word
2019-04-14 not vca, but control.
2019-04-16 Added control group pwm init and vca interface
2019-04-16 Do comments, rename timing files
2019-04-17 Forgot time.c/h, add lbr, empty pcb files
2019-04-20 Add lots more parts, make sch of progress
2019-04-21 Add filter, start lin-expo converter
2019-04-21 add 2162 datatsheet
2019-04-30 move 4voice to 1voice, do lin->exp
2019-05-17 Finish 1-voice brd, start making it work
2019-05-22 Made v2
2019-05-26 Start v3
2019-05-31 Add LED blink code, Update schem with LED R values
2019-06-22 Found error in sch values around lin->exp converter
2019-06-22 Add another resource
2019-06-26 Add gitignore
2019-06-26 Add simulation files
2019-07-01 Changed board rails, transferred sims to pcb
2019-07-01 Standardize part vals
2019-07-20 Finished latest layout
